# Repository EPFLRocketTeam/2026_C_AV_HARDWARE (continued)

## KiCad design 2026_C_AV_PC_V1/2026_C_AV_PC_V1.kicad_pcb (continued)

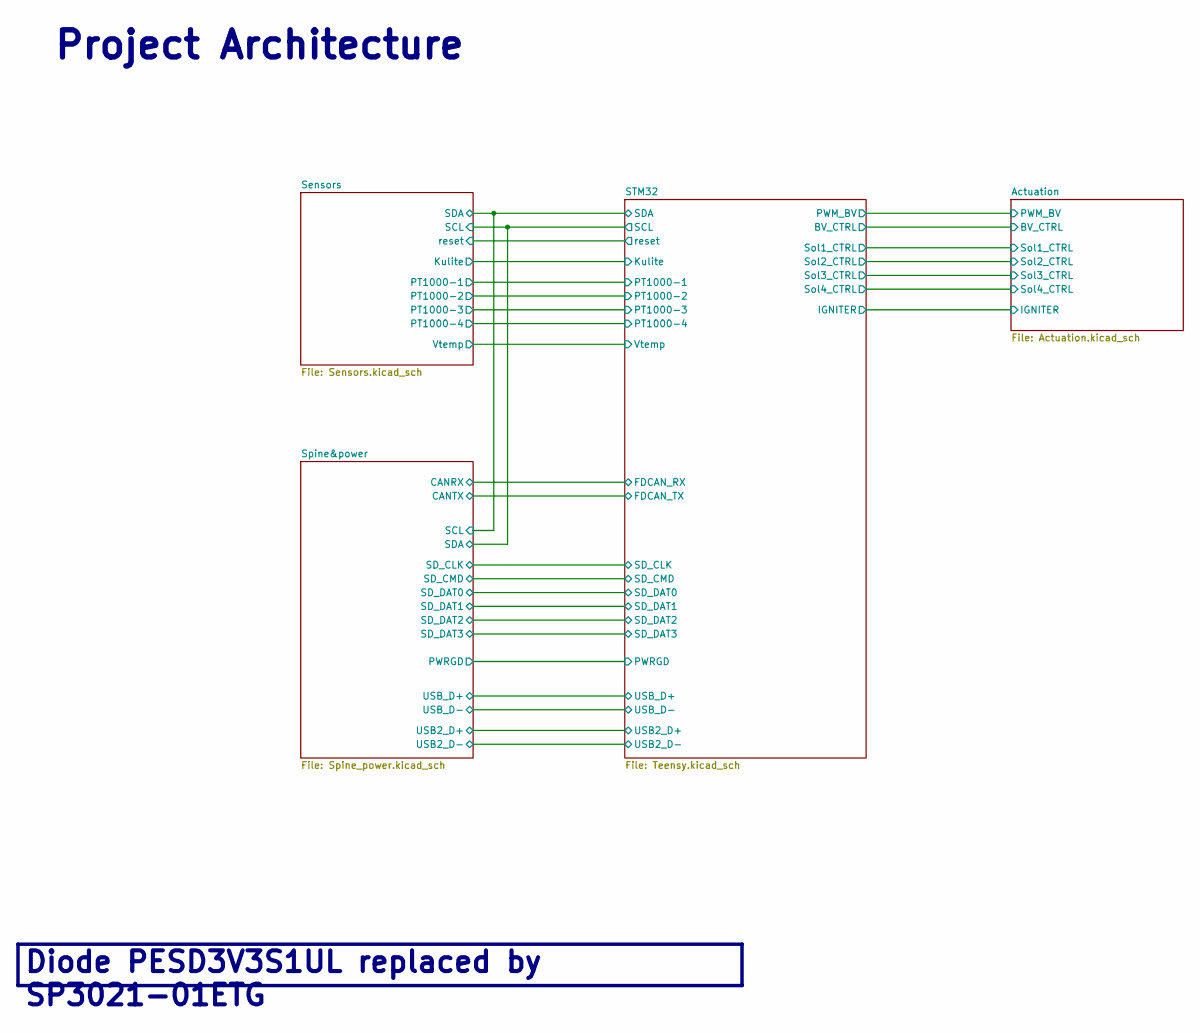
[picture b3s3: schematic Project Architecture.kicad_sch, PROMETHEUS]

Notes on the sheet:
Project Architecture
Diode PESD3V3S1UL replaced by SP3021-01ETG

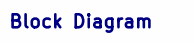
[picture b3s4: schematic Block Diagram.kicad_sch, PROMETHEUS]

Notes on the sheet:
Block Diagram

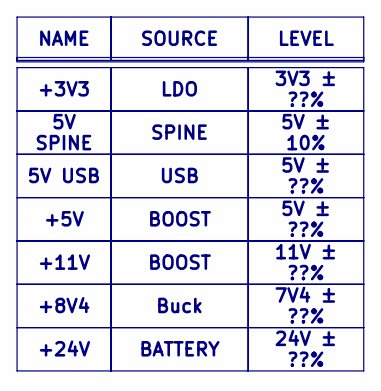
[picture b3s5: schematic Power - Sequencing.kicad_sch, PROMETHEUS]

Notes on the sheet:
5V SPINE
BOOST
5V ± ??%
3V3 ± ??%
+24V
SOURCE
7V4 ± ??%
Buck
BOOST
+5V
SPINE
5V USB
11V ± ??%
+11V
USB
LDO
+8V4
BATTERY
24V ± ??%
5V ± 10%
LEVEL
+3V3
NAME

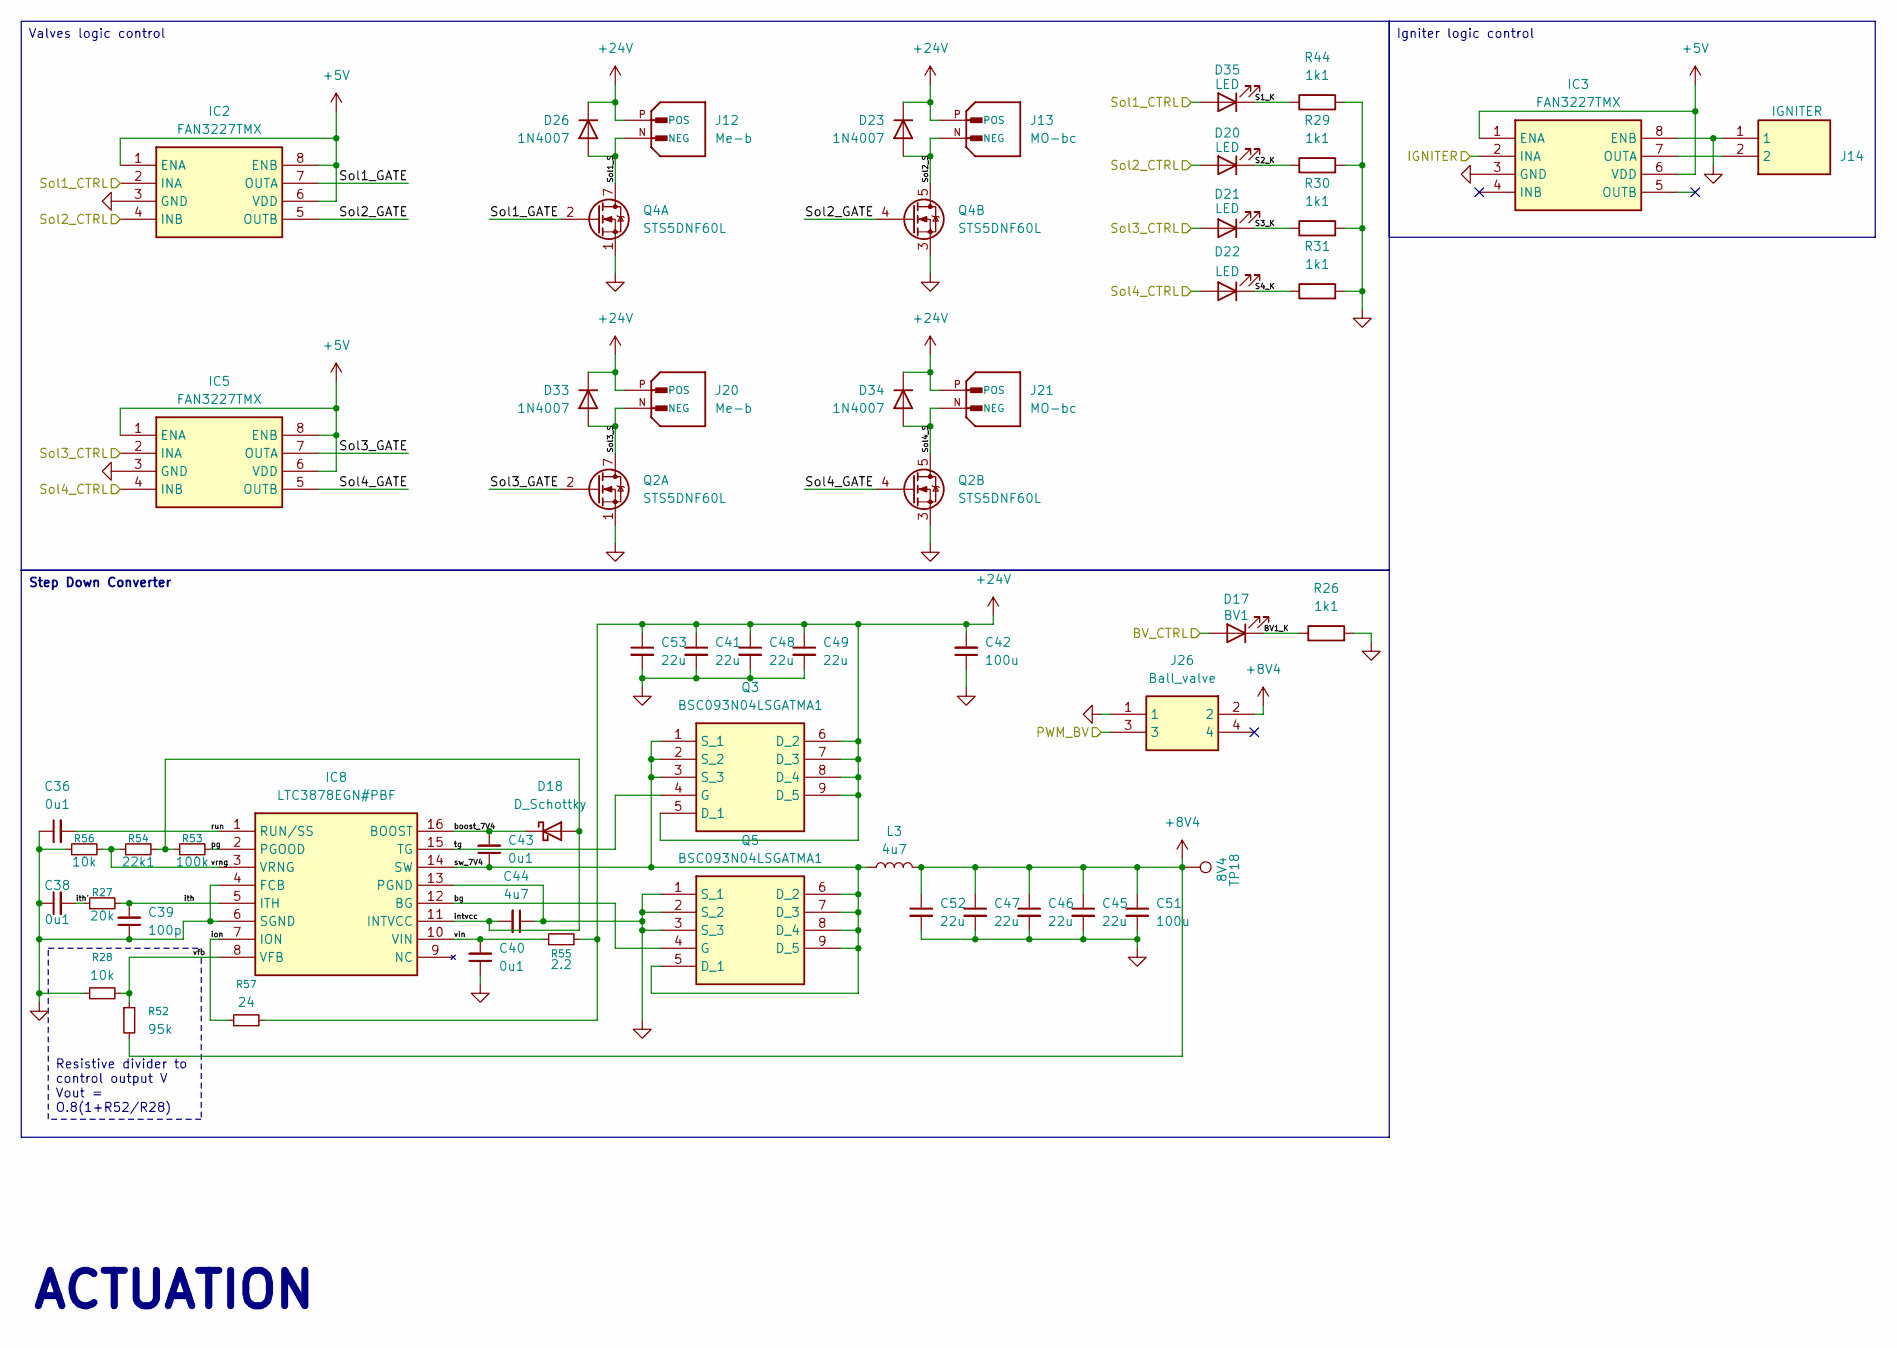
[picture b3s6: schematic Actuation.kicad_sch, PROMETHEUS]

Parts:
C36, C38, C40, C43: 0u1; C_0603_1608Metric
C39: 100p; C_0603_1608Metric
C41, C48, C49, C53: 22u; C_0805_2012Metric
C42, C51: 100u; C_Elec_6.3x5.8; Mouser No 80-A768EB107M1ELAE36
C44: 4u7; C_0603_1608Metric
C45, C46, C47, C52: 22u; C_0402_1005Metric
D17: BV1; LED_0603_1608Metric
D18: D_Schottky; SOT-23-3; Mouser No 522-ZLLS1000TA
D20, D21, D22, D35: LED; LED_0603_1608Metric
D23, D26, D33, D34: 1N4007; D_SOD-123F
IC2, IC3, IC5: FAN3227TMX; Mouser Part Number 512-FAN3227TMX
IC8: LTC3878EGN#PBF; SOP64P601X175-16N; Mouser Part Number 584-LTC3878EGN#PBF
J12, J20: Me-b; AMASS_XT30U-M_1x02_P5.0mm_Vertical; PARTREV V1.2
J13, J21: MO-bc; AMASS_XT30U-M_1x02_P5.0mm_Vertical; PARTREV V1.2
J14: IGNITER; 530470210; Mouser Part Number 538-53047-0210
J26: Ball_valve; 1053142104; Mouser Part Number 538-105314-2104
L3: 4u7; SRP7030CA2R2M; Mouser No 710-74437346047
Q2, Q4: STS5DNF60L; SOIC-8_3.9x4.9mm_P1.27mm
Q3, Q5: BSC093N04LSGATMA1; BSC340N08NS3G; Mouser Part Number 726-BSC093N04LSGATMA
R26, R29, R30, R31, R44: 1k1; R_0603_1608Metric
R27: 20k; R_0603_1608Metric
R28, R56: 10k; R_0603_1608Metric
R52: 95k; R_0603_1608Metric
R53: 100k; R_0603_1608Metric
R54: 22k1; R_0603_1608Metric
R55: 2.2; R_0603_1608Metric
R57: 24; R_0603_1608Metric
TP18: 8V4; TestPoint_THTPad_D1.5mm_Drill0.7mm

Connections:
+5V: IC2.1 (ENA), IC2.6 (VDD), IC2.8 (ENB), IC3.1 (ENA), IC3.6 (VDD), IC5.1 (ENA), IC5.6 (VDD), IC5.8 (ENB); also elsewhere on the board
+8V4: C45.1, C46.1, C47.1, C51.1, C52.1, J26.2, L3.2, R52.2, TP18.1
+24V: C41.1, C42.2, C48.1, C49.1, C53.1, D23.1 (K), D26.1 (K), D33.1 (K), D34.1 (K), J12.P (POS), J13.P (POS), J20.P (POS), J21.P (POS), Q3.5 (D_1), Q3.6 (D_2), Q3.7 (D_3), Q3.8 (D_4), Q3.9 (D_5), R55.2, R57.2; also elsewhere on the board
/Project Architecture/Actuation/BV1_K: D17.1 (K), R26.1
/Project Architecture/Actuation/BV_CTRL: D17.2 (A); also elsewhere on the board
/Project Architecture/Actuation/IGNITER: IC3.2 (INA); also elsewhere on the board
/Project Architecture/Actuation/PWM_BV: J26.3; also elsewhere on the board
/Project Architecture/Actuation/S1_K: D35.1 (K), R44.1
/Project Architecture/Actuation/S2_K: D20.1 (K), R29.1
/Project Architecture/Actuation/S3_K: D21.1 (K), R30.1
/Project Architecture/Actuation/S4_K: D22.1 (K), R31.1
/Project Architecture/Actuation/Sol1_CTRL: D35.2 (A), IC2.2 (INA); also elsewhere on the board
/Project Architecture/Actuation/Sol1_GATE: IC2.7 (OUTA), Q4.2 (G1)
/Project Architecture/Actuation/Sol1_S: D26.2 (A), J12.N (NEG), Q4.7 (D1), Q4.8 (D1)
/Project Architecture/Actuation/Sol2_CTRL: D20.2 (A), IC2.4 (INB); also elsewhere on the board
/Project Architecture/Actuation/Sol2_GATE: IC2.5 (OUTB), Q4.4 (G2)
/Project Architecture/Actuation/Sol2_S: D23.2 (A), J13.N (NEG), Q4.5 (D2), Q4.6 (D2)
/Project Architecture/Actuation/Sol3_CTRL: D21.2 (A), IC5.2 (INA); also elsewhere on the board
/Project Architecture/Actuation/Sol3_GATE: IC5.7 (OUTA), Q2.2 (G1)
/Project Architecture/Actuation/Sol3_S: D33.2 (A), J20.N (NEG), Q2.7 (D1), Q2.8 (D1)
/Project Architecture/Actuation/Sol4_CTRL: D22.2 (A), IC5.4 (INB); also elsewhere on the board
/Project Architecture/Actuation/Sol4_GATE: IC5.5 (OUTB), Q2.4 (G2)
/Project Architecture/Actuation/Sol4_S: D34.2 (A), J21.N (NEG), Q2.5 (D2), Q2.6 (D2)
/Project Architecture/Actuation/bg: IC8.12 (BG), Q5.4 (G)
/Project Architecture/Actuation/boost_7V4: C43.2, D18.1 (K), IC8.16 (BOOST)
/Project Architecture/Actuation/intvcc: C44.2, D18.2 (A), IC8.11 (INTVCC), R53.1, R54.2
/Project Architecture/Actuation/ion: IC8.7 (ION), R57.1
/Project Architecture/Actuation/ith: C39.2, IC8.5 (ITH), R27.2
/Project Architecture/Actuation/ith': C38.2, R27.1
/Project Architecture/Actuation/pg: IC8.2 (PGOOD), R53.2
/Project Architecture/Actuation/run: C36.2, IC8.1 (RUN/SS)
/Project Architecture/Actuation/sw_7V4: C43.1, IC8.14 (SW), L3.1, Q3.1 (S_1), Q3.2 (S_2), Q3.3 (S_3), Q5.5 (D_1), Q5.6 (D_2), Q5.7 (D_3), Q5.8 (D_4), Q5.9 (D_5)
/Project Architecture/Actuation/tg: IC8.15 (TG), Q3.4 (G)
/Project Architecture/Actuation/vfb: IC8.8 (VFB), R28.2, R52.1
/Project Architecture/Actuation/vin: C40.2, IC8.10 (VIN), R55.1
/Project Architecture/Actuation/vrng: IC8.3 (VRNG), R54.1, R56.2
GND: C36.1, C38.1, C39.1, C40.1, C41.2, C42.1, C44.1, C45.2, C46.2, C47.2, C48.2, C49.2, C51.2, C52.2, C53.2, IC2.3 (GND), IC3.3 (GND), IC3.8 (ENB), IC5.3 (GND), IC8.4 (FCB), IC8.6 (SGND), IC8.13 (PGND), J14.1, J26.1, Q2.1 (S1), Q2.3 (S2), Q4.1 (S1), Q4.3 (S2), Q5.1 (S_1), Q5.2 (S_2), Q5.3 (S_3), R26.2, R28.1, R29.2, R30.2, R31.2, R44.2, R56.1; also elsewhere on the board
unnamed: IC3.7 (OUTA), J14.2

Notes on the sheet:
ACTUATION
Step Down Converter
Valves logic control
Resistive divider to control output V Vout = O.8(1+R52/R28)
Igniter logic control

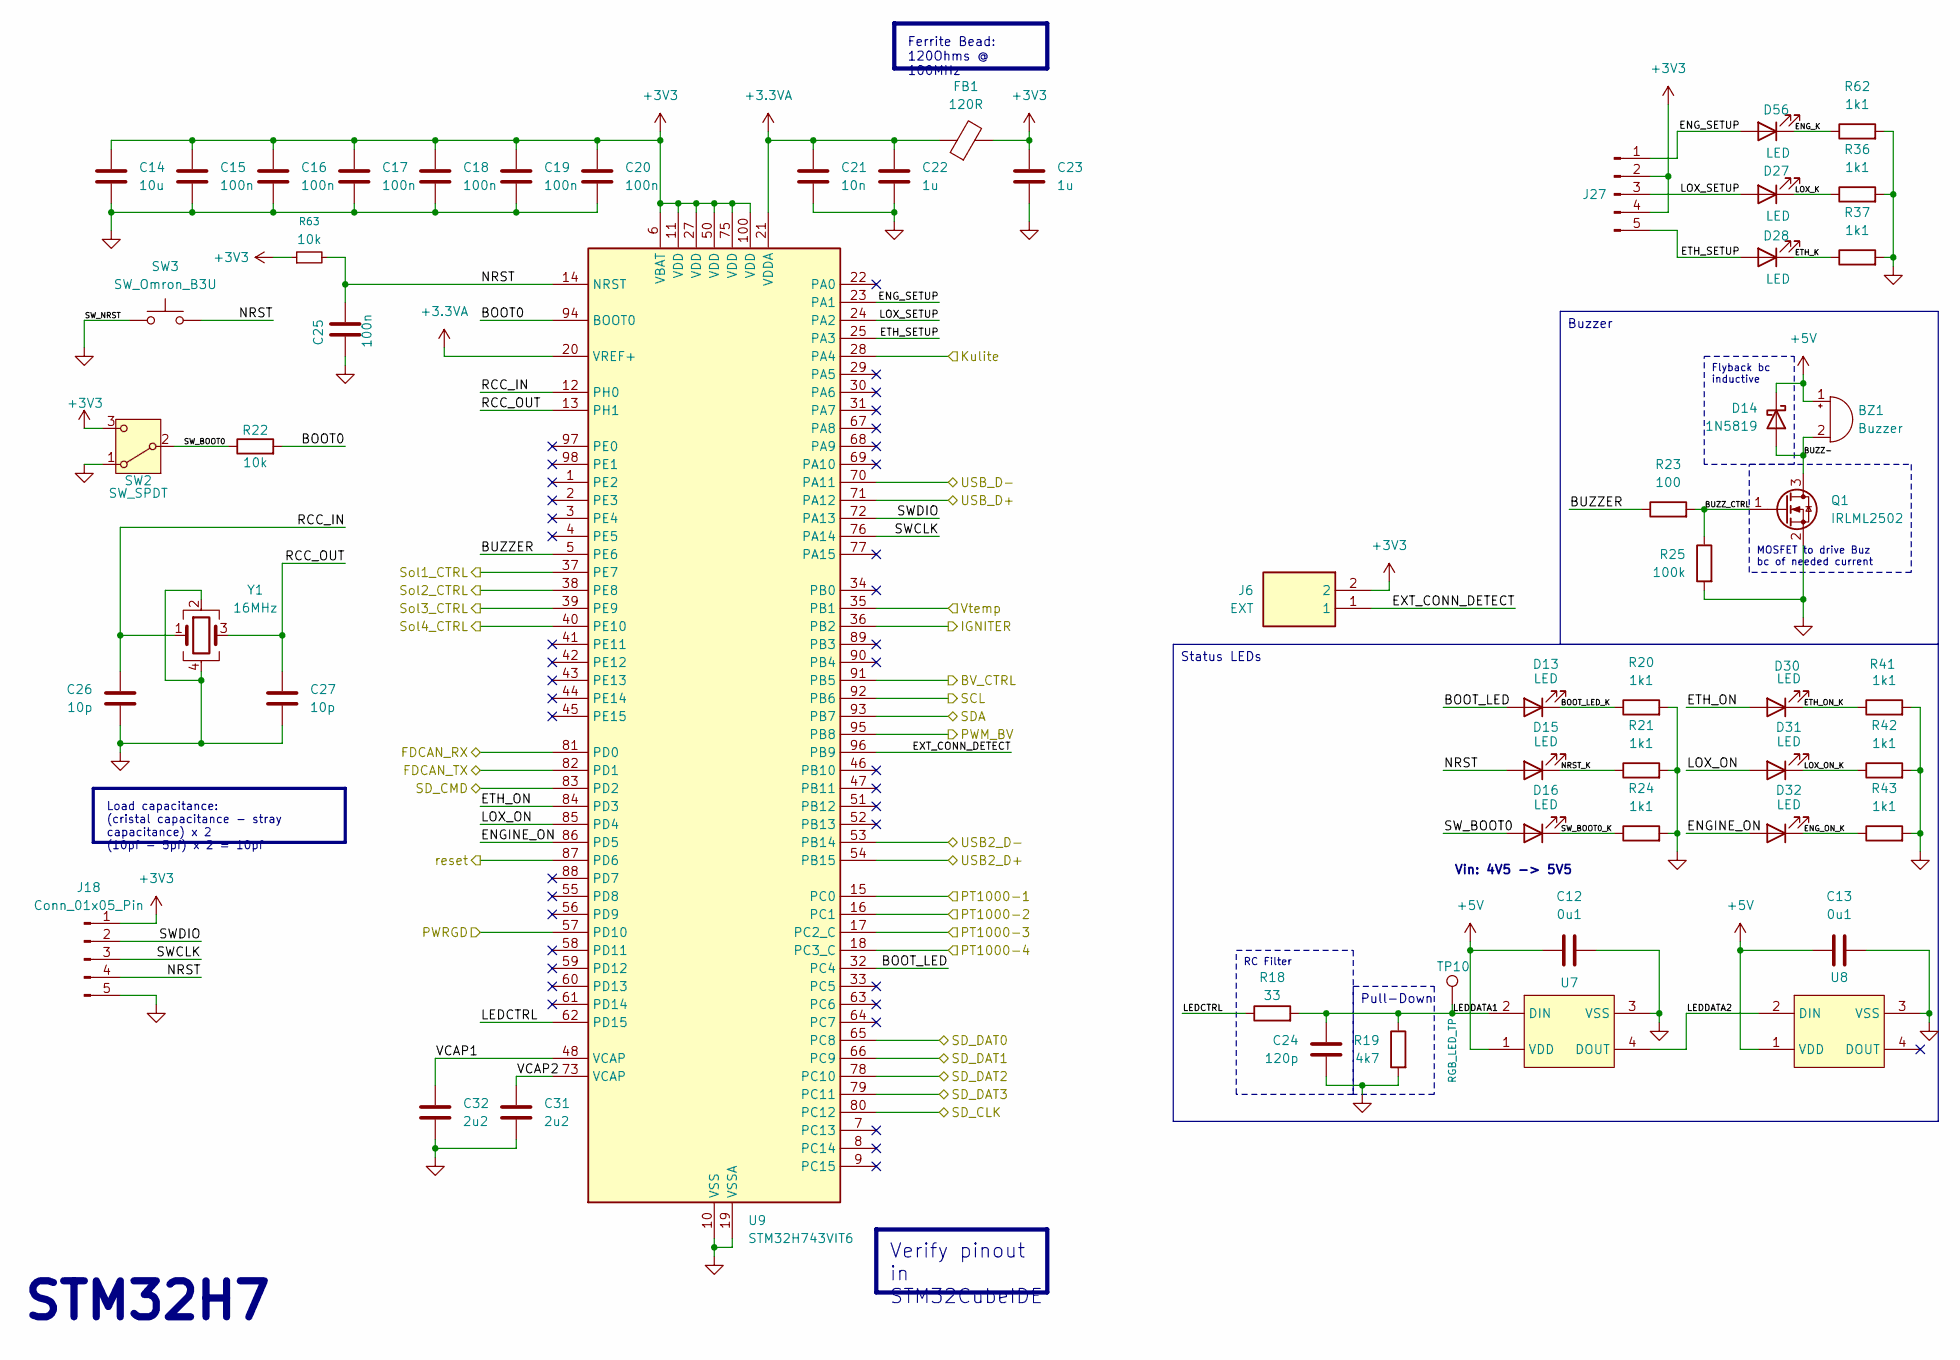
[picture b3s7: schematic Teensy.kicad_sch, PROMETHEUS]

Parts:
BZ1: Buzzer; Buzzer_TDK_PS1240P02BT_D12.2mm_H6.5mm
C12, C13: 0u1; C_0603_1608Metric
C14: 10u; C_0603_1608Metric
C15, C16, C17, C18, C19, C20: 100n; C_0402_1005Metric
C21: 10n; C_0402_1005Metric
C22, C23: 1u; C_0402_1005Metric
C24: 120p; C_0603_1608Metric
C25: 100n; C_0603_1608Metric
C26, C27: 10p; C_0402_1005Metric
C31, C32: 2u2; C_0402_1005Metric
D13, D15, D16, D27, D28, D30, D31, D32, D56: LED; LED_0603_1608Metric
D14: 1N5819; D_SOD-123
FB1: 120R; L_0603_1608Metric
J6: EXT; 530470210; Mouser Part Number 538-53047-0210
J18: Conn_01x05_Pin; PinHeader_1x05_P2.54mm_Vertical_SMD_Pin1Left
J27: Conn_01x05_Pin; PinHeader_1x05_P1.00mm_Vertical_SMD_Pin1Right
Q1: IRLML2502; SOT-23
R18: 33; R_0603_1608Metric
R19: 4k7; R_0603_1608Metric
R20, R21, R24, R36, R37, R41, R42, R43, R62: 1k1; R_0603_1608Metric
R22, R63: 10k; R_0603_1608Metric
R23: 100; R_0603_1608Metric
R25: 100k; R_0603_1608Metric
SW2: SW_SPDT; SW_SPDT_PCM12
SW3: SW_Omron_B3U; SW_SPST_B3U-1000P
TP10: RGB_LED_TP; TestPoint_THTPad_D1.5mm_Drill0.7mm
U7: RGBLED_1; NEW_RGB_LED
U8: RGBLED_2; NEW_RGB_LED
U9: STM32H743VIT6; LQFP-100_14x14mm_P0.5mm
Y1: 16MHz; Crystal_SMD_2016-4Pin_2.0x1.6mm

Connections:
+3.3VA: C21.1, C22.1, FB1.1, U9.20 (VREF+), U9.21 (VDDA)
+3V3: C14.1, C15.1, C16.1, C17.1, C18.1, C19.1, C20.1, C23.1, FB1.2, J6.2, J18.1, J27.2, J27.4, R63.1, SW2.3 (C), U9.6 (VBAT), U9.11 (VDD), U9.27 (VDD), U9.50 (VDD), U9.75 (VDD), U9.100 (VDD); also elsewhere on the board
+5V: BZ1.1 (+), C12.1, C13.1, D14.1 (K), U7.1 (VDD), U8.1 (VDD); also elsewhere on the board
/Project Architecture/Actuation/BV_CTRL: U9.91 (PB5); also elsewhere on the board
/Project Architecture/Actuation/IGNITER: U9.36 (PB2); also elsewhere on the board
/Project Architecture/Actuation/PWM_BV: U9.95 (PB8); also elsewhere on the board
/Project Architecture/Actuation/Sol1_CTRL: U9.37 (PE7); also elsewhere on the board
/Project Architecture/Actuation/Sol2_CTRL: U9.38 (PE8); also elsewhere on the board
/Project Architecture/Actuation/Sol3_CTRL: U9.39 (PE9); also elsewhere on the board
/Project Architecture/Actuation/Sol4_CTRL: U9.40 (PE10); also elsewhere on the board
/Project Architecture/STM32/BOOT0: R22.2, U9.94 (BOOT0)
/Project Architecture/STM32/BOOT_LED: D13.2 (A), U9.32 (PC4)
/Project Architecture/STM32/BOOT_LED_K: D13.1 (K), R20.1
/Project Architecture/STM32/BUZZ-: BZ1.2 (-), D14.2 (A), Q1.3 (D)
/Project Architecture/STM32/BUZZER: R23.1, U9.5 (PE6)
/Project Architecture/STM32/BUZZ_CTRL: Q1.1 (G), R23.2, R25.1
/Project Architecture/STM32/ENGINE_ON: D32.2 (A), U9.86 (PD5)
/Project Architecture/STM32/ENG_K: D56.1 (K), R62.1
/Project Architecture/STM32/ENG_ON_K: D32.1 (K), R43.1
/Project Architecture/STM32/ENG_SETUP: D56.2 (A), J27.1, U9.23 (PA1)
/Project Architecture/STM32/ETH_K: D28.1 (K), R37.1
/Project Architecture/STM32/ETH_ON: D30.2 (A), U9.84 (PD3)
/Project Architecture/STM32/ETH_ON_K: D30.1 (K), R41.1
/Project Architecture/STM32/ETH_SETUP: D28.2 (A), J27.5, U9.25 (PA3)
/Project Architecture/STM32/EXT_CONN_DETECT: J6.1, U9.96 (PB9)
/Project Architecture/STM32/FDCAN_RX: U9.81 (PD0); also elsewhere on the board
/Project Architecture/STM32/FDCAN_TX: U9.82 (PD1); also elsewhere on the board
/Project Architecture/STM32/Kulite: U9.28 (PA4); also elsewhere on the board
/Project Architecture/STM32/LEDCTRL: R18.1, U9.62 (PD15)
/Project Architecture/STM32/LEDDATA1: C24.2, R18.2, R19.1, TP10.1, U7.2 (DIN)
/Project Architecture/STM32/LEDDATA2: U7.4 (DOUT), U8.2 (DIN)
/Project Architecture/STM32/LOX_K: D27.1 (K), R36.1
/Project Architecture/STM32/LOX_ON: D31.2 (A), U9.85 (PD4)
/Project Architecture/STM32/LOX_ON_K: D31.1 (K), R42.1
/Project Architecture/STM32/LOX_SETUP: D27.2 (A), J27.3, U9.24 (PA2)
/Project Architecture/STM32/NRST: C25.2, D15.2 (A), J18.4, R63.2, SW3.2, U9.14 (NRST)
/Project Architecture/STM32/NRST_K: D15.1 (K), R21.1
/Project Architecture/STM32/PT1000-1: U9.15 (PC0); also elsewhere on the board
/Project Architecture/STM32/PT1000-2: U9.16 (PC1); also elsewhere on the board
/Project Architecture/STM32/PT1000-3: U9.17 (PC2_C); also elsewhere on the board
/Project Architecture/STM32/PT1000-4: U9.18 (PC3_C); also elsewhere on the board
/Project Architecture/STM32/PWRGD: U9.57 (PD10); also elsewhere on the board
/Project Architecture/STM32/RCC_IN: C26.1, U9.12 (PH0), Y1.1
/Project Architecture/STM32/RCC_OUT: C27.1, U9.13 (PH1), Y1.3
/Project Architecture/STM32/SCL: U9.92 (PB6); also elsewhere on the board
/Project Architecture/STM32/SDA: U9.93 (PB7); also elsewhere on the board
/Project Architecture/STM32/SD_CLK: U9.80 (PC12); also elsewhere on the board
/Project Architecture/STM32/SD_CMD: U9.83 (PD2); also elsewhere on the board
/Project Architecture/STM32/SD_DAT0: U9.65 (PC8); also elsewhere on the board
/Project Architecture/STM32/SD_DAT1: U9.66 (PC9); also elsewhere on the board
/Project Architecture/STM32/SD_DAT2: U9.78 (PC10); also elsewhere on the board
/Project Architecture/STM32/SD_DAT3: U9.79 (PC11); also elsewhere on the board
/Project Architecture/STM32/SWCLK: J18.3, U9.76 (PA14)
/Project Architecture/STM32/SWDIO: J18.2, U9.72 (PA13)
/Project Architecture/STM32/SW_BOOT0: D16.2 (A), R22.1, SW2.2 (B)
/Project Architecture/STM32/SW_BOOT0_K: D16.1 (K), R24.1
/Project Architecture/STM32/USB2_D+: U9.54 (PB15); also elsewhere on the board
/Project Architecture/STM32/USB2_D-: U9.53 (PB14); also elsewhere on the board
/Project Architecture/STM32/USB_D+: U9.71 (PA12); also elsewhere on the board
/Project Architecture/STM32/USB_D-: U9.70 (PA11); also elsewhere on the board
/Project Architecture/STM32/VCAP1: C32.1, U9.48 (VCAP)
/Project Architecture/STM32/VCAP2: C31.1, U9.73 (VCAP)
/Project Architecture/STM32/Vtemp: U9.35 (PB1); also elsewhere on the board
/Project Architecture/STM32/reset: U9.87 (PD6); also elsewhere on the board
GND: C12.2, C13.2, C14.2, C15.2, C16.2, C17.2, C18.2, C19.2, C20.2, C21.2, C22.2, C23.2, C24.1, C25.1, C26.2, C27.2, C31.2, C32.2, J18.5, Q1.2 (S), R19.2, R20.2, R21.2, R24.2, R25.2, R36.2, R37.2, R41.2, R42.2, R43.2, R62.2, SW2.1 (A), SW3.1, U7.3 (VSS), U8.3 (VSS), U9.10 (VSS), U9.19 (VSSA), U9.26 (VSS), U9.49 (VSS), U9.74 (VSS), U9.99 (VSS), Y1.2, Y1.4; also elsewhere on the board

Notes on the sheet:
STM32H7
Vin: 4V5 -> 5V5
RC Filter
Load capacitance: (cristal capacitance - stray capacitance) x 2 (10pf - 5pf) x 2 = 10pf
MOSFET to drive Buz bc of needed current
Verify pinout in STM32CubeIDE
Ferrite Bead: 120Ohms @ 100MHz
Status LEDs
Buzzer
Flyback bc inductive
Pull-Down

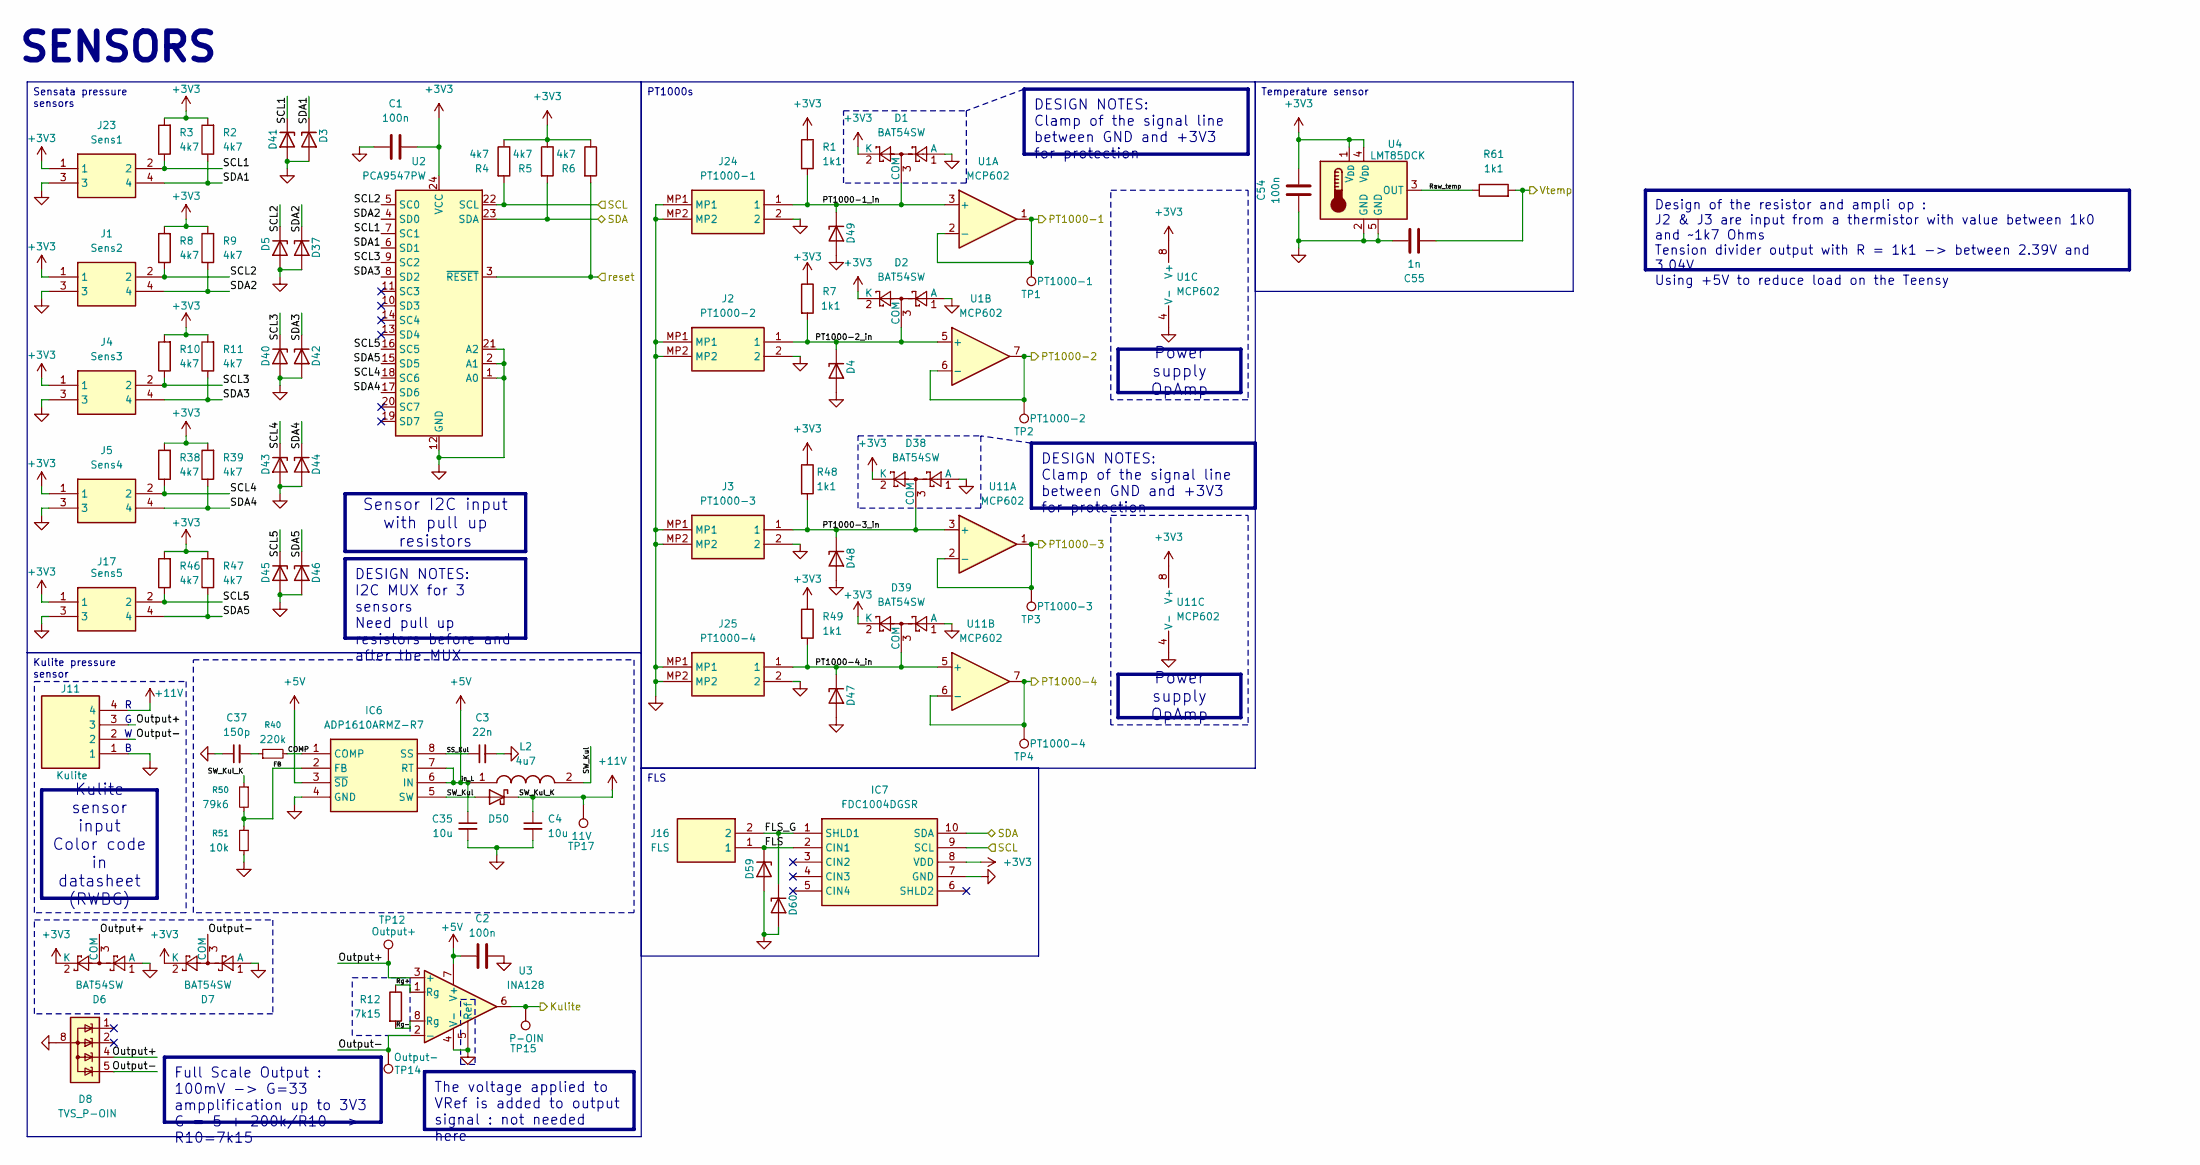
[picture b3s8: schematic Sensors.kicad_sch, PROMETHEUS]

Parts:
C1, C2, C54: 100n; C_0603_1608Metric
C3: 22n; C_0603_1608Metric
C4, C35: 10u; C_0603_1608Metric
C37: 150p; C_0603_1608Metric
C55: 1n; C_0603_1608Metric
D1, D2, D6, D7, D38, D39: BAT54SW; SOT-323_SC-70
D3, D5, D37, D41: PESD3V3S1UL; D_SOD-882; Mouser SP3205-01ETG
D4, D40, D42, D43, D44, D45, D46, D47, D48, D49, D59, D60: PESD3V3S1UL; D_SOD-882; Mouser 771-PESD3V3L1UL315
D8: TVS_P-OIN; PESD4USB3UTBSQX
D50: D_Schottky; D_SOD-523
IC6: ADP1610ARMZ-R7; SOP65P490X110-8N; Mouser Part Number 584-ADP1610ARMZ-R7
IC7: FDC1004DGSR; SOP50P490X110-10N; Mouser Part Number 595-FDC1004DGSR
J1: Sens2; SHDRRA4W55P200_2X2_665X640X630P; Mouser Part Number 538-87833-0419
J2: PT1000-2; 5015680207; Mouser Part Number 538-501568-0207
J3: PT1000-3; 5015680207; Mouser Part Number 538-501568-0207
J4: Sens3; SHDRRA4W55P200_2X2_665X640X630P; Mouser Part Number 538-87833-0419
J5: Sens4; SHDRRA4W55P200_2X2_665X640X630P; Mouser Part Number 538-87833-0419
J11: Kulite; SHDR4W64P0X250_1X4_1246X650X700P; Mouser Part Number 538-35312-0460
J16: FLS; 530470210; Mouser Part Number 538-53047-0210
J17: Sens5; SHDRRA4W55P200_2X2_665X640X630P; Mouser Part Number 538-87833-0419
J23: Sens1; SHDRRA4W55P200_2X2_665X640X630P; Mouser Part Number 538-87833-0419
J24: PT1000-1; 5015680207; Mouser Part Number 538-501568-0207
J25: PT1000-4; 5015680207; Mouser Part Number 538-501568-0207
L2: 4u7; WE-TPC_282892; Mouser Part Number 710-744025004
R1, R7, R48, R49, R61: 1k1; R_0603_1608Metric
R2, R3, R4, R5, R6, R8, R9, R10, R11, R38, R39, R46, R47: 4k7; R_0603_1608Metric
R12: 7k15; R_0603_1608Metric
R40: 220k; R_0603_1608Metric
R50: 79k6; R_0603_1608Metric
R51: 10k; R_0603_1608Metric
TP1: PT1000-1; TestPoint_THTPad_D1.5mm_Drill0.7mm
TP2: PT1000-2; TestPoint_THTPad_D1.5mm_Drill0.7mm
TP3: PT1000-3; TestPoint_THTPad_D1.5mm_Drill0.7mm
TP4: PT1000-4; TestPoint_THTPad_D1.5mm_Drill0.7mm
TP12: Output+; TestPoint_THTPad_D1.5mm_Drill0.7mm
TP14: Output-; TestPoint_THTPad_D1.5mm_Drill0.7mm
TP15: P-OIN; TestPoint_THTPad_D1.5mm_Drill0.7mm
TP17: 11V; TestPoint_THTPad_D1.5mm_Drill0.7mm
U1, U11: MCP602; SOIC-8_3.9x4.9mm_P1.27mm
U2: PCA9547PW; TSSOP-24_4.4x5mm_P0.4mm
U3: INA128; SOIC-8_3.9x4.9mm_P1.27mm
U4: LMT85DCK; SOT-353_SC-70-5

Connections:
+3V3: C1.1, C54.2, D1.2 (K), D2.2 (K), D6.2 (K), D7.2 (K), D38.2 (K), D39.2 (K), IC7.8 (VDD), J1.1, J4.1, J5.1, J17.1, J23.1, R1.1, R2.2, R3.2, R4.1, R5.1, R6.1, R7.1, R8.2, R9.2, R10.2, R11.2, R38.2, R39.2, R46.2, R47.2, R48.1, R49.1, U1.8 (V+), U2.24 (VCC), U4.1 (V_{DD}), U4.4 (V_{DD}), U11.8 (V+); also elsewhere on the board
+5V: C2.1, C35.1, IC6.3 (~SD), IC6.6 (IN), IC6.7 (RT), L2.1, U3.7 (V+); also elsewhere on the board
+11V: C4.1, D50.1 (K), J11.4, R50.1, TP17.1
/Project Architecture/STM32/Kulite: TP15.1, U3.6; also elsewhere on the board
/Project Architecture/STM32/PT1000-1: TP1.1, U1.1, U1.2 (-); also elsewhere on the board
/Project Architecture/STM32/PT1000-2: TP2.1, U1.6 (-), U1.7; also elsewhere on the board
/Project Architecture/STM32/PT1000-3: TP3.1, U11.1, U11.2 (-); also elsewhere on the board
/Project Architecture/STM32/PT1000-4: TP4.1, U11.6 (-), U11.7; also elsewhere on the board
/Project Architecture/STM32/SCL: IC7.9 (SCL), R4.2, U2.22 (SCL); also elsewhere on the board
/Project Architecture/STM32/SDA: IC7.10 (SDA), R5.2, U2.23 (SDA); also elsewhere on the board
/Project Architecture/STM32/Vtemp: C55.1, R61.2; also elsewhere on the board
/Project Architecture/STM32/reset: R6.2, U2.3 (~RESET); also elsewhere on the board
/Project Architecture/Sensors/COMP: IC6.1 (COMP), R40.2
/Project Architecture/Sensors/FB: IC6.2 (FB), R50.2, R51.1
/Project Architecture/Sensors/FLS: D59.1 (K), IC7.2 (CIN1), J16.1
/Project Architecture/Sensors/FLS_G: D60.1 (K), IC7.1 (SHLD1), J16.2
/Project Architecture/Sensors/Output+: D6.3 (COM), D8.4, D8.7, J11.3, TP12.1, U3.3 (+)
/Project Architecture/Sensors/Output-: D7.3 (COM), D8.5, D8.6, J11.2, TP14.1, U3.2 (-)
/Project Architecture/Sensors/PT1000-1_in: D1.3 (COM), D49.1 (K), J24.1, R1.2, U1.3 (+)
/Project Architecture/Sensors/PT1000-2_in: D2.3 (COM), D4.1 (K), J2.1, R7.2, U1.5 (+)
/Project Architecture/Sensors/PT1000-3_in: D38.3 (COM), D48.1 (K), J3.1, R48.2, U11.3 (+)
/Project Architecture/Sensors/PT1000-4_in: D39.3 (COM), D47.1 (K), J25.1, R49.2, U11.5 (+)
/Project Architecture/Sensors/Raw_temp: R61.1, U4.3 (OUT)
/Project Architecture/Sensors/Rg+: R12.1, U3.1 (Rg)
/Project Architecture/Sensors/Rg-: R12.2, U3.8 (Rg)
/Project Architecture/Sensors/SCL1: D41.1 (K), J23.2, R3.1, U2.7 (SC1)
/Project Architecture/Sensors/SCL2: D5.1 (K), J1.2, R8.1, U2.5 (SC0)
/Project Architecture/Sensors/SCL3: D40.1 (K), J4.2, R10.1, U2.9 (SC2)
/Project Architecture/Sensors/SCL4: D43.1 (K), J5.2, R38.1, U2.18 (SC6)
/Project Architecture/Sensors/SCL5: D45.1 (K), J17.2, R46.1, U2.16 (SC5)
/Project Architecture/Sensors/SDA1: D3.1 (K), J23.4, R2.1, U2.6 (SD1)
/Project Architecture/Sensors/SDA2: D37.1 (K), J1.4, R9.1, U2.4 (SD0)
/Project Architecture/Sensors/SDA3: D42.1 (K), J4.4, R11.1, U2.8 (SD2)
/Project Architecture/Sensors/SDA4: D44.1 (K), J5.4, R39.1, U2.17 (SD6)
/Project Architecture/Sensors/SDA5: D46.1 (K), J17.4, R47.1, U2.15 (SD5)
/Project Architecture/Sensors/SS_Kul: C3.1, IC6.8 (SS)
/Project Architecture/Sensors/SW_Kul: D50.2 (A), IC6.5 (SW), L2.2
GND: C1.2, C2.2, C3.2, C4.2, C35.2, C37.1, C54.1, C55.2, D1.1 (A), D2.1 (A), D3.2 (A), D4.2 (A), D5.2 (A), D6.1 (A), D7.1 (A), D8.3, D8.8, D37.2 (A), D38.1 (A), D39.1 (A), D40.2 (A), D41.2 (A), D42.2 (A), D43.2 (A), D44.2 (A), D45.2 (A), D46.2 (A), D47.2 (A), D48.2 (A), D49.2 (A), D59.2 (A), D60.2 (A), IC6.4 (GND), IC7.7 (GND), J1.3, J2.2, J2.MP1, J2.MP2, J3.2, J3.MP1, J3.MP2, J4.3, J5.3, J11.1, J17.3, J23.3, J24.2, J24.MP1, J24.MP2, J25.2, J25.MP1, J25.MP2, R51.2, U1.4 (V-), U2.1 (A0), U2.2 (A1), U2.12 (GND), U2.21 (A2), U3.4 (V-), U3.5 (Ref), U4.2 (GND), U4.5 (GND), U11.4 (V-); also elsewhere on the board
unnamed: C37.2, R40.1

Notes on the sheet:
SENSORS
PT1000s
Kulite pressure sensor
DESIGN NOTES: Clamp of the signal line between GND and +3V3 for protection
Sensata pressure sensors
Kulite sensor input Color code in datasheet (RWBG)
Power supply OpAmp
FLS
The voltage applied to VRef is added to output signal : not needed here
Temperature sensor
DESIGN NOTES: I2C MUX for 3 sensors Need pull up resistors before and after the MUX
Design of the resistor and ampli op : J2 & J3 are input from a thermistor with value between 1k0 and ~1k7 Ohms Tension divider output with R = 1k1 -> between 2.39V and 3.04V Using +5V to reduce load on the Teensy
Full Scale Output : 100mV -> G=33 ampplification up to 3V3 G = 5 + 200k/R10 -> R10=7k15
Sensor I2C input with pull up resistors
